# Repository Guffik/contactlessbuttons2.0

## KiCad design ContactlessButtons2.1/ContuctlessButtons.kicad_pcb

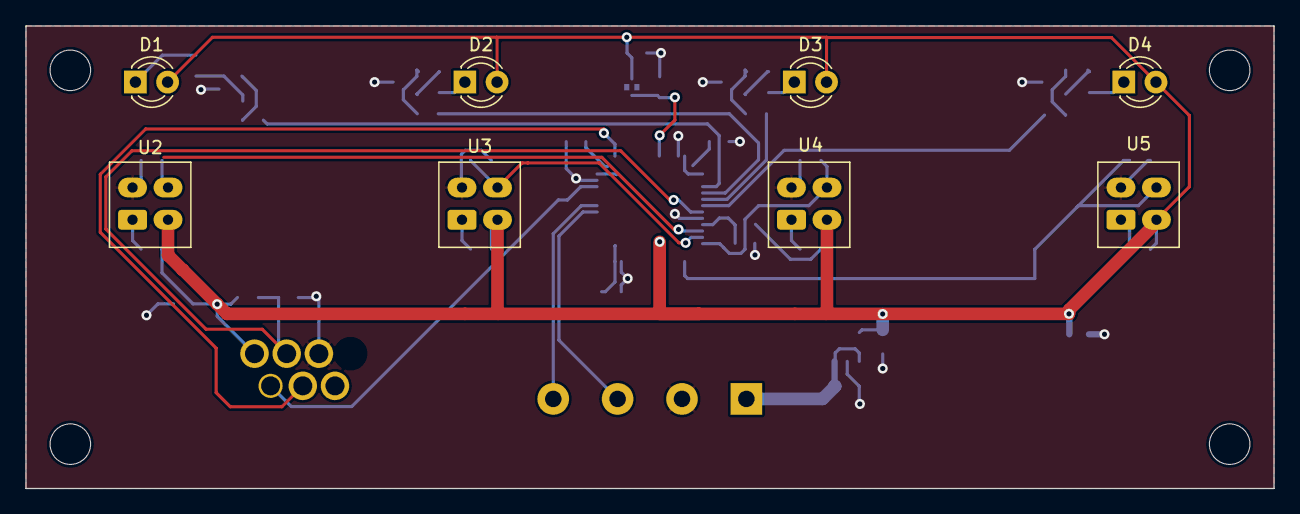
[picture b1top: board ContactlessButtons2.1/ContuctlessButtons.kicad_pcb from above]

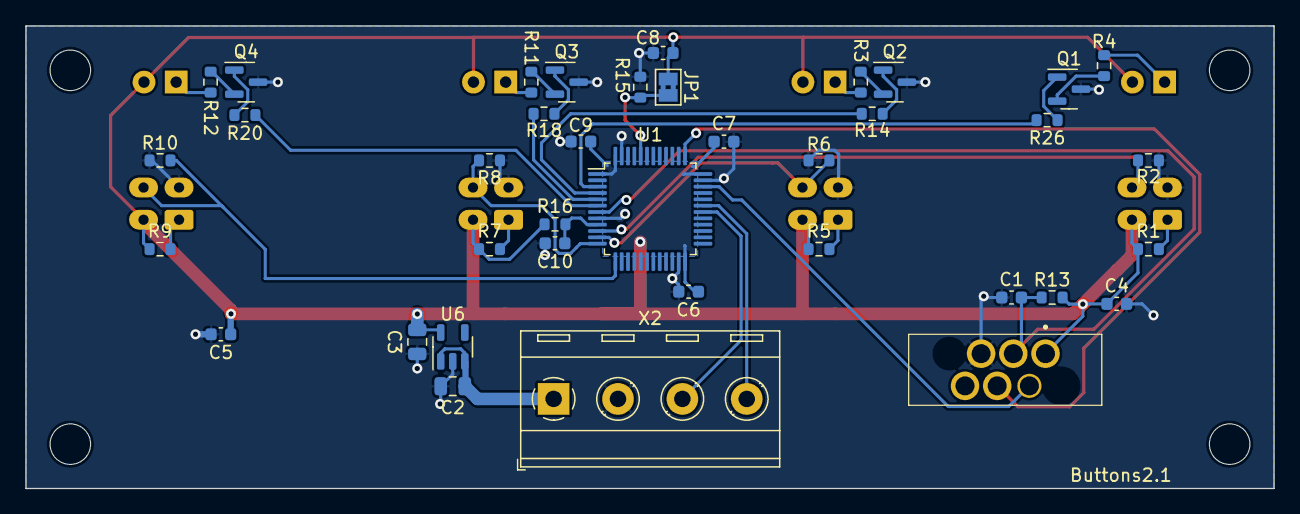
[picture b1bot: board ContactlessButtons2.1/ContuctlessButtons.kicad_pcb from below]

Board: 2 copper layers, 98.5 x 36.5 mm, 50 parts (38 on the bottom side), 34 nets.

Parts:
C1, C4, C5, C6, C7, C8, C9, C10: 100n; C_0603_1608Metric
C2, C3: 10u; C_0805_2012Metric
D1, D2, D3, D4: LED; LED_D3.0mm
H1, H2, H3, H4: MountingHole; MountingHole_3.2mm_M3
JP1: BOOT0; SolderJumper-2_P1.3mm_Bridged2Bar_Pad1.0x1.5mm
Q1, Q2, Q3, Q4: NPN; SOT-23
R1, R5, R7, R9: 470R; R_0603_1608Metric
R2, R6, R8, R16: 4K7; R_0603_1608Metric
R3, R4, R11, R12: 470Ω; R_0603_1608Metric
R10: 4k7; R_0603_1608Metric
R13, R15: 1K; R_0603_1608Metric
R14, R18, R20, R26: 4.7kΩ; R_0603_1608Metric
U1: STM32L071CBTx; LQFP-48_7x7mm_P0.5mm
U2, U3, U4, U5: ITR20001/T; ITR20001
U6: MCP1824T-3302E/OT; SOT-23-5
X1: CONN_6; 490107670612
X2: CONN_4; TerminalBlock_RND_205-00289_1x04_P5.08mm_Horizontal

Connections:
+3.3V: C3.1, C4.1, C5.1, C6.1, C7.1, C8.1, C9.1, D1.2 (A), D2.2 (A), D3.2 (A), D4.2 (A), JP1.1 (A), R1.1, R5.1, R7.1, R9.1, R13.1, R16.1, U1.1 (VDD), U1.24 (VDD), U1.36 (VDDIO2), U1.48 (VDD), U2.4 (C), U3.4 (C), U4.4 (C), U5.4 (C), U6.5 (VOUT), X1.1
/5V: C2.1, U6.1 (VIN), U6.3 (~SHDN), X2.1
/Light0: R26.1, U1.3 (PC14)
/Light1: R14.1, U1.4 (PC15)
/Light2: R18.1, U1.5 (PH0)
/Light3: R20.1, U1.6 (PH1)
/NRST: C1.2, R13.2, U1.7 (NRST), X1.3
/Pin0: R2.1, U1.10 (PA0), U2.3 (E)
/Pin1: R6.1, U1.11 (PA1), U3.3 (E)
/Pin2: R8.1, U1.12 (PA2), U4.3 (E)
/Pin3: R10.1, U1.13 (PA3), U5.3 (E)
/SYS_SWCLK: U1.37 (PA14), X1.4
/SYS_SWDIO: U1.34 (PA13), X1.2
/USART1_RX: U1.31 (PA10), X2.4
/USART1_TX: U1.30 (PA9), X2.3
GNDD: C1.1, C2.2, C3.2, C4.2, C5.2, C6.2, C7.2, C8.2, C9.2, C10.2, Q1.3 (E), Q2.3 (E), Q3.3 (E), Q4.3 (E), R2.2, R6.2, R8.2, R10.2, R15.1, U1.8 (VSSA), U1.23 (VSS), U1.35 (VSS), U1.47 (VSS), U2.2 (K), U3.2 (K), U4.2 (K), U5.2 (K), U6.2 (GND), X1.5, X2.2
unnamed: D1.1 (K), R4.2
unnamed: D2.1 (K), R3.2
unnamed: D3.1 (K), R11.2
unnamed: D4.1 (K), R12.2
unnamed: JP1.2 (B), R15.2, U1.44 (BOOT0)
unnamed: Q1.1 (B), R26.2
unnamed: Q1.2 (C), R4.1
unnamed: Q2.1 (B), R14.2
unnamed: Q2.2 (C), R3.1
unnamed: Q3.1 (B), R18.2
unnamed: Q3.2 (C), R11.1
unnamed: Q4.1 (B), R20.2
unnamed: Q4.2 (C), R12.1
unnamed: C10.1, R16.2, U1.9 (VDDA)
unnamed: R1.2, U2.1 (A)
unnamed: R5.2, U3.1 (A)
unnamed: R7.2, U4.1 (A)
unnamed: R9.2, U5.1 (A)

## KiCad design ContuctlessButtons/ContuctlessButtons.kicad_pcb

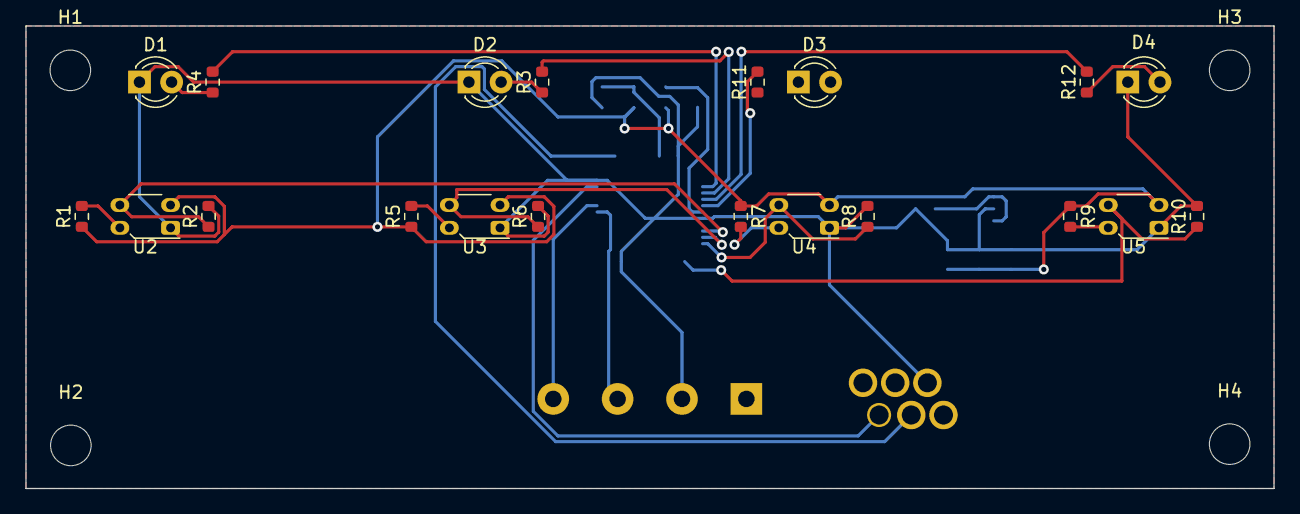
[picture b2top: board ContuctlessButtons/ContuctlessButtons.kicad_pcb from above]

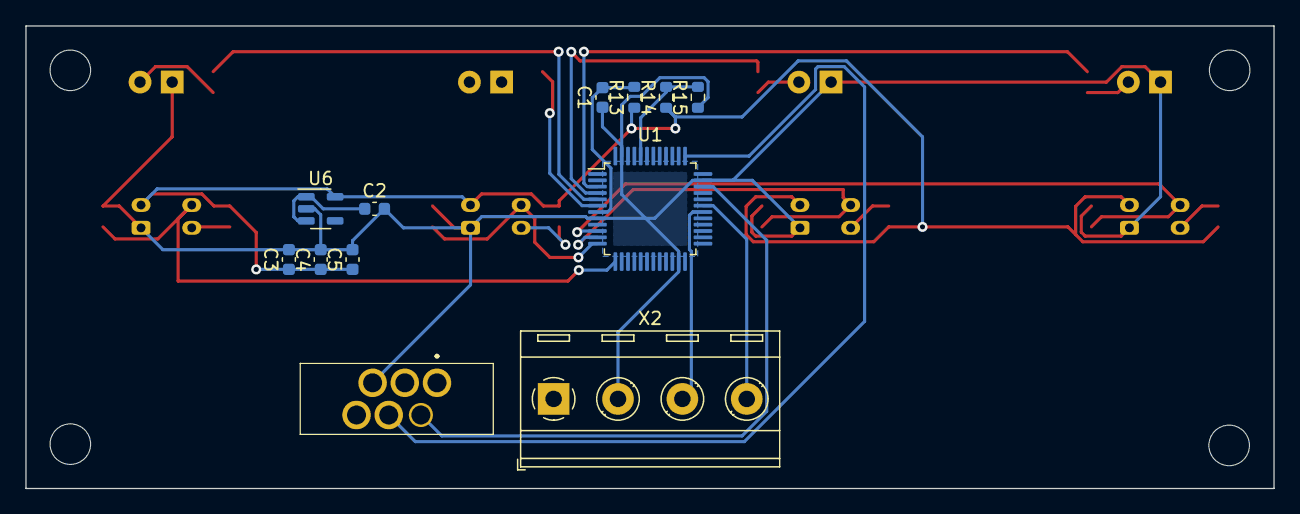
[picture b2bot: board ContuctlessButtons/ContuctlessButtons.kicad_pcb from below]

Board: 2 copper layers, 98.5 x 36.5 mm, 36 parts (12 on the bottom side), 25 nets.

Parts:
C1, C2, C3, C4, C5: C_Small; C_0603_1608Metric
D1, D2, D3, D4: LED; LED_D3.0mm
H1, H2, H3, H4: MountingHole; MountingHole_3.2mm_M3
R1, R3, R4, R5, R7, R9, R11, R12: 470R; R_0603_1608Metric
R2, R6, R8, R10: 4K7; R_0603_1608Metric
R13, R14, R15: R; R_0603_1608Metric
U1: STM32L071CBTx; LQFP-48_7x7mm_P0.5mm
U2, U3, U4, U5: ITR20001/T; Everlight_ITR8307F43
U6: MCP1824T-3302E/OT; SOT-23-5
X1: CONN_6; 490107670612
X2: CONN_4; TerminalBlock_RND_205-00289_1x04_P5.08mm_Horizontal

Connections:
+3.3V: C3.1, C4.1, C5.1, R1.1, R5.1, R7.1, R9.1, R13.1, R14.1, U2.3 (C), U3.3 (C), U4.3 (C), U5.3 (C), U6.5 (VOUT)
/Light0: R4.2, U1.3 (PC14)
/Light1: R3.2, U1.4 (PC15)
/Light2: R12.2, U1.5 (PH0)
/Light3: R11.2, U1.6 (PH1)
/Pin0: R2.1, U1.10 (PA0), U2.4 (E)
/Pin1: R6.1, U1.11 (PA1), U3.4 (E)
/Pin2: R8.1, U1.12 (PA2), U4.4 (E)
/Pin3: R10.1, U1.13 (PA3), U5.4 (E)
/SYS_SWCLK: U1.37 (PA14), X1.4
/SYS_SWDIO: U1.34 (PA13), X1.2
/USART1_RX: U1.31 (PA10), X2.4
/USART1_TX: U1.30 (PA9), X2.3
GNDD: C1.1, C2.2, C3.2, C4.2, C5.2, D1.1 (K), D2.1 (K), D3.1 (K), D4.1 (K), R2.2, R6.2, R8.2, R10.2, R15.1, U1.8 (VSSA), U1.23 (VSS), U1.35 (VSS), U1.47 (VSS), U2.1 (K), U3.1 (K), U4.1 (K), U5.1 (K), U6.2 (GND), X1.5, X2.2
unnamed: D1.2 (A), R4.1
unnamed: D2.2 (A), R3.1
unnamed: D3.2 (A), R11.1
unnamed: D4.2 (A), R12.1
unnamed: R14.2, R15.2, U1.44 (BOOT0)
unnamed: C1.2, R13.2, U1.7 (NRST)
unnamed: R1.2, U2.2 (A)
unnamed: R5.2, U3.2 (A)
unnamed: R7.2, U4.2 (A)
unnamed: R9.2, U5.2 (A)
unnamed: C2.1, U6.1 (VIN), U6.3 (~SHDN)
